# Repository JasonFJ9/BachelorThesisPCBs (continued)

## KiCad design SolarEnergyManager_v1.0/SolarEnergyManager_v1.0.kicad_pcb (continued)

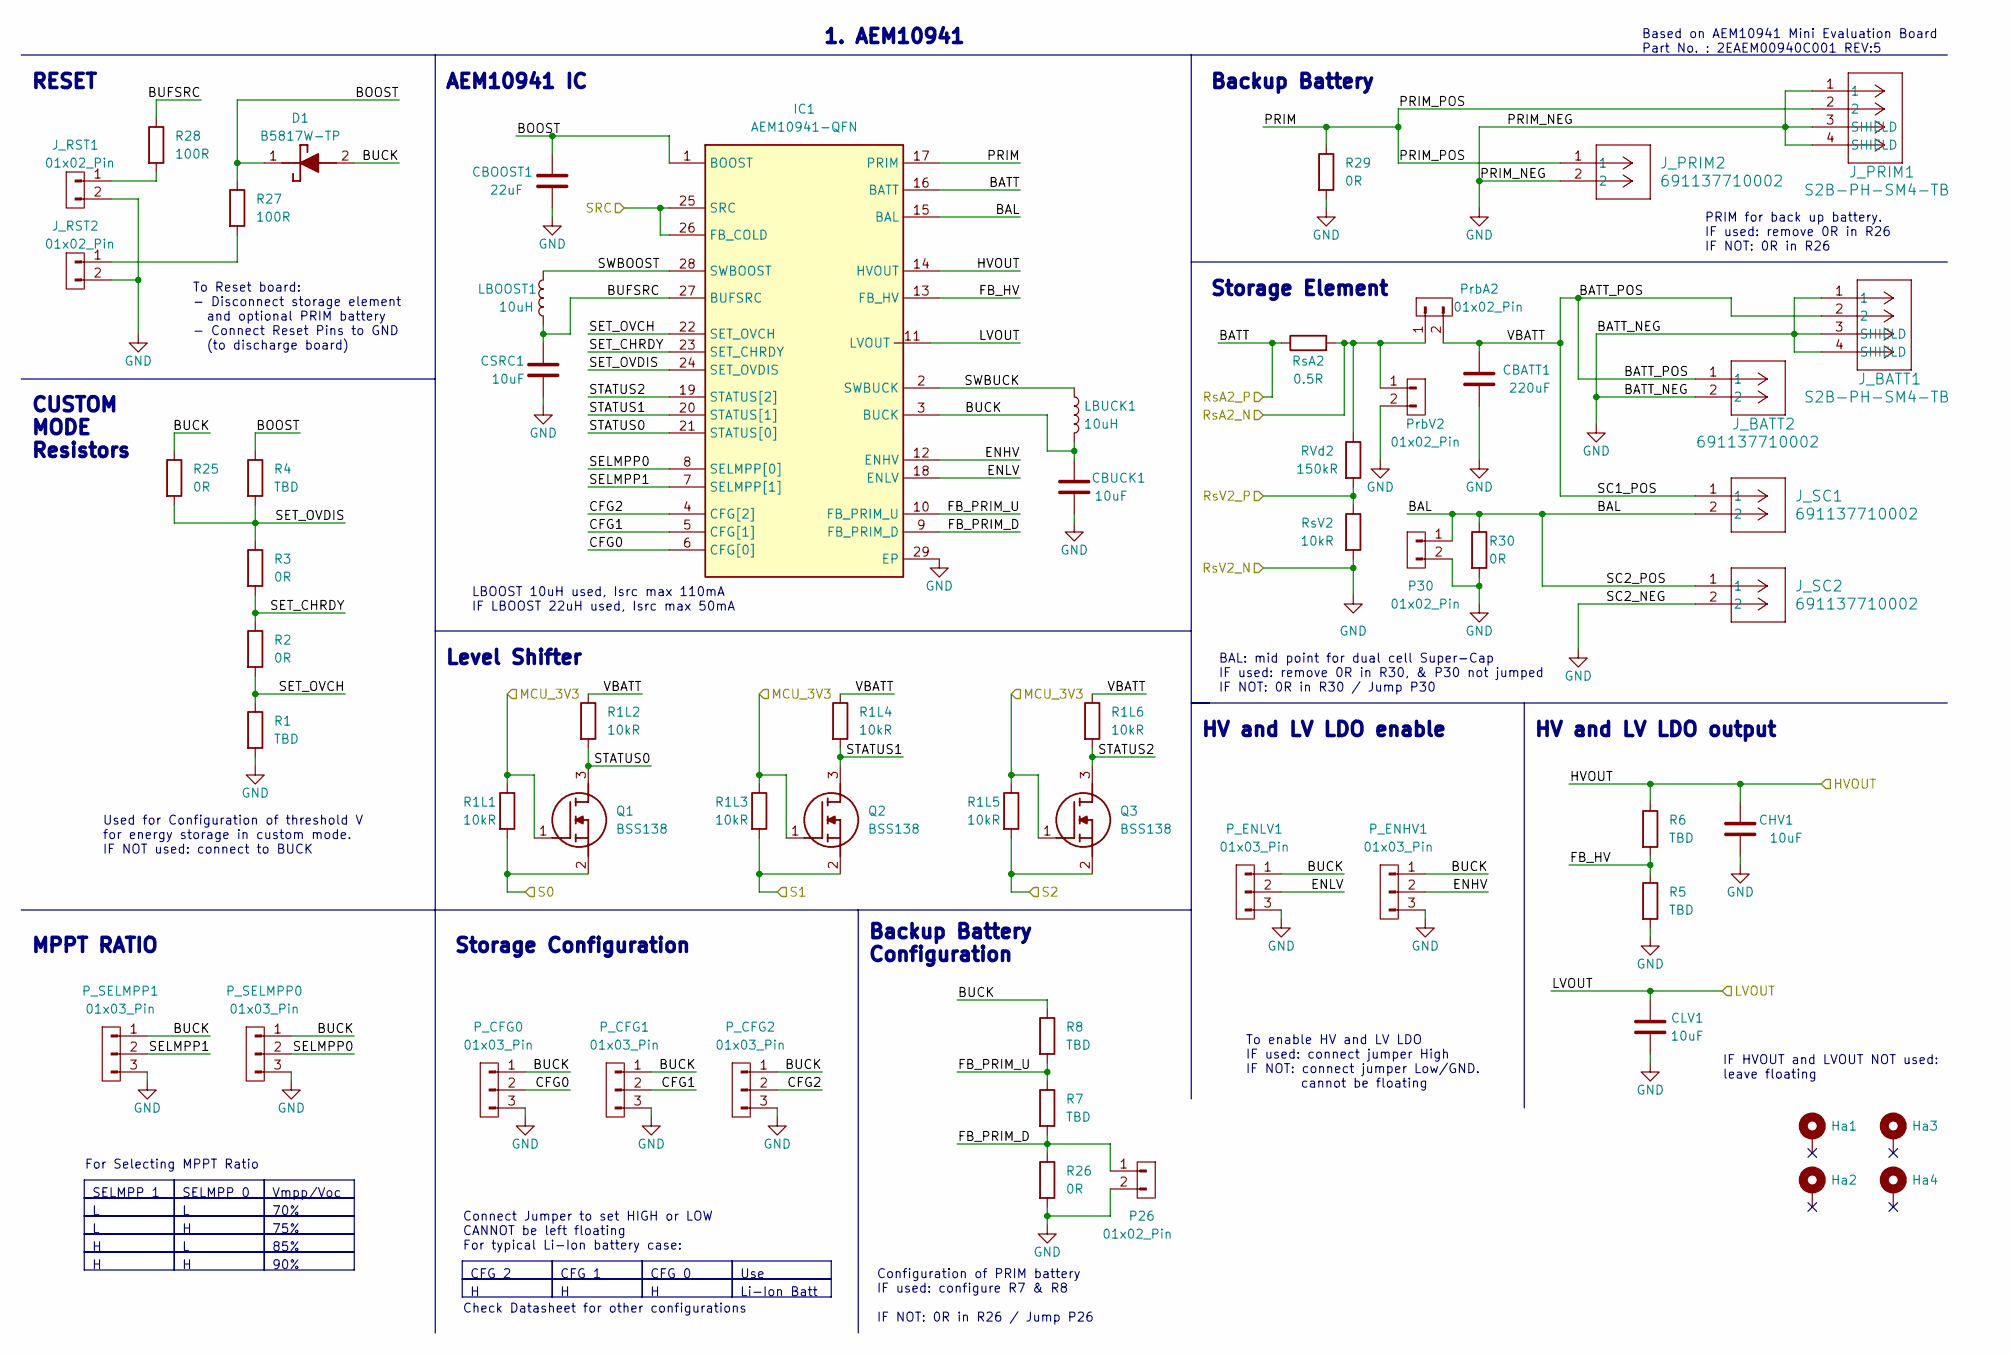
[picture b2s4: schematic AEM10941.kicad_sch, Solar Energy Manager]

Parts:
CBATT1: 220uF; C_1206_3216Metric
CBOOST1: 22uF; C_0603_1608Metric
CBUCK1: 10uF; C_0603_1608Metric
CHV1: 10uF; C_0603_1608Metric
CLV1: 10uF; C_0603_1608Metric
CSRC1: 10uF; C_0603_1608Metric
D1: B5817W-TP; SOD3716X135N; Mouser Part Number 833-B5817W-TP
Ha1, Ha2, Ha3, Ha4: MountingHole_Pad; MountingHole_3.2mm_M3_Pad
IC1: AEM10941-QFN; QFN50P500X500X90-29N-D; Mouser Part Number 120-AEM10941-QFN
J_BATT1: S2B-PH-SM4-TB; CONN_S2B-PH-SM4-TB_JST
J_BATT2: 691137710002; CONN2_710002_WRE
J_PRIM1: S2B-PH-SM4-TB; CONN_S2B-PH-SM4-TB_JST
J_PRIM2: 691137710002; CONN2_710002_WRE
J_RST1, J_RST2: 01x02_Pin; PinHeader_1x02_P2.54mm_Vertical
J_SC1, J_SC2: 691137710002; CONN2_710002_WRE
LBOOST1: 10uH; L_Vishay_IFSC-1515AH_4x4x1.8mm
LBUCK1: 10uH; L_0603_1608Metric
P26, P30: 01x02_Pin; PinHeader_1x02_P2.54mm_Vertical
P_CFG0, P_CFG1, P_CFG2: 01x03_Pin; PinHeader_1x03_P2.54mm_Vertical
P_ENHV1: 01x03_Pin; PinHeader_1x03_P2.54mm_Vertical
P_ENLV1: 01x03_Pin; PinHeader_1x03_P2.54mm_Vertical
P_SELMPP0, P_SELMPP1: 01x03_Pin; PinHeader_1x03_P2.54mm_Vertical
PrbA2: 01x02_Pin; PinHeader_1x02_P2.54mm_Vertical
PrbV2: 01x02_Pin; PinHeader_1x02_P2.54mm_Vertical
Q1, Q2, Q3: BSS138; SOT95P240X120-3N; Mouser Part Number 512-BSS138
R1, R4, R5, R6, R7, R8: TBD; R_0603_1608Metric
R1L1, R1L2, R1L3, R1L4, R1L5, R1L6: 10kR; R_0402_1005Metric
R2, R3, R25, R26, R29, R30: 0R; R_0603_1608Metric
R27, R28: 100R; R_0603_1608Metric
RVd2: 150kR; R_0402_1005Metric
RsA2: 0.5R; R_0805_2012Metric
RsV2: 10kR; R_0402_1005Metric

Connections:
/3v3_MCU: Q1.1 (G), Q2.1 (G), Q3.1 (G), R1L1.1, R1L3.1, R1L5.1; also elsewhere on the board
/AEM10941/BAL: IC1.15 (BAL), J_SC1.2, J_SC2.1, P30.1, R30.1
/AEM10941/BATT_POS: CBATT1.1, J_BATT1.2, J_BATT2.1, J_SC1.1, PrbA2.2, R1L2.1, R1L4.1, R1L6.1
/AEM10941/BOOST: CBOOST1.1, D1.1 (K), IC1.1 (BOOST), R4.1, R27.1
/AEM10941/BUCK: CBUCK1.1, D1.2 (A), IC1.3 (BUCK), LBUCK1.2, P_CFG0.1, P_CFG1.1, P_CFG2.1, P_ENHV1.1, P_ENLV1.1, P_SELMPP0.1, P_SELMPP1.1, R8.1, R25.1
/AEM10941/BUFSRC: CSRC1.1, IC1.27 (BUFSRC), LBOOST1.2, R28.1
/AEM10941/CFG0: IC1.6 (CFG[0]), P_CFG0.2
/AEM10941/CFG1: IC1.5 (CFG[1]), P_CFG1.2
/AEM10941/CFG2: IC1.4 (CFG[2]), P_CFG2.2
/AEM10941/ENHV: IC1.12 (ENHV), P_ENHV1.2
/AEM10941/ENLV: IC1.18 (ENLV), P_ENLV1.2
/AEM10941/FB_HV: IC1.13 (FB_HV), R5.1, R6.2
/AEM10941/FB_PRIM_D: IC1.9 (FB_PRIM_D), P26.1, R7.2, R26.1
/AEM10941/FB_PRIM_U: IC1.10 (FB_PRIM_U), R7.1, R8.2
/AEM10941/HVOUT: CHV1.1, IC1.14 (HVOUT), R6.1; also elsewhere on the board
/AEM10941/LVOUT: CLV1.1, IC1.11 (LVOUT); also elsewhere on the board
/AEM10941/PRIM: IC1.17 (PRIM), J_PRIM1.2, J_PRIM2.1, R29.1
/AEM10941/SELMPP0: IC1.8 (SELMPP[0]), P_SELMPP0.2
/AEM10941/SELMPP1: IC1.7 (SELMPP[1]), P_SELMPP1.2
/AEM10941/SET_CHRDY: IC1.23 (SET_CHRDY), R2.1, R3.2
/AEM10941/SET_OVCH: IC1.22 (SET_OVCH), R1.1, R2.2
/AEM10941/SET_OVDIS: IC1.24 (SET_OVDIS), R3.1, R4.2, R25.2
/AEM10941/SRC: IC1.25 (SRC), IC1.26 (FB_COLD); also elsewhere on the board
/AEM10941/STATUS0: IC1.21 (STATUS[0]), Q1.3 (D), R1L2.2
/AEM10941/STATUS1: IC1.20 (STATUS[1]), Q2.3 (D), R1L4.2
/AEM10941/STATUS2: IC1.19 (STATUS[2]), Q3.3 (D), R1L6.2
/AEM10941/SWBOOST: IC1.28 (SWBOOST), LBOOST1.1
/AEM10941/SWBUCK: IC1.2 (SWBUCK), LBUCK1.1
/AEM_S0: Q1.2 (S), R1L1.2; also elsewhere on the board
/AEM_S1: Q2.2 (S), R1L3.2; also elsewhere on the board
/AEM_S2: Q3.2 (S), R1L5.2; also elsewhere on the board
/s_3A_N: PrbA2.1, PrbV2.1, RVd2.1, RsA2.2; also elsewhere on the board
/s_3A_P: IC1.16 (BATT), RsA2.1; also elsewhere on the board
/s_4A_P: RVd2.2, RsV2.1; also elsewhere on the board
GND: CBATT1.2, CBOOST1.2, CBUCK1.2, CHV1.2, CLV1.2, CSRC1.2, IC1.29 (EP), J_BATT1.1, J_BATT1.3 (SHIELD), J_BATT1.4 (SHIELD), J_BATT2.2, J_PRIM1.1, J_PRIM1.3 (SHIELD), J_PRIM1.4 (SHIELD), J_PRIM2.2, J_RST1.2, J_RST2.2, J_SC2.2, P26.2, P30.2, P_CFG0.3, P_CFG1.3, P_CFG2.3, P_ENHV1.3, P_ENLV1.3, P_SELMPP0.3, P_SELMPP1.3, PrbV2.2, R1.2, R5.2, R26.2, R29.2, R30.2, RsV2.2; also elsewhere on the board
unnamed: J_RST1.1, R28.2
unnamed: J_RST2.1, R27.2

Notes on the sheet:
90%
Li-Ion Batt
75%
70%
Vmpp/Voc
CFG 0
CFG 2
SELMPP 0
Use
CFG 1
85%
SELMPP 1
IF HVOUT and LVOUT NOT used: leave floating
Check Datasheet for other configurations
Storage Configuration
Connect Jumper to set HIGH or LOW CANNOT be left floating For typical Li-Ion battery case:
CUSTOM MODE Resistors
For Selecting MPPT Ratio
HV and LV LDO output
RESET
HV and LV LDO enable
Backup Battery
To enable HV and LV LDO IF used: connect jumper High IF NOT: connect jumper Low/GND. cannot be floating
1. AEM10941
Based on AEM10941 Mini Evaluation Board Part No. : 2EAEM00940C001 REV:5
BAL: mid point for dual cell Super-Cap IF used: remove 0R in R30, & P30 not jumped IF NOT: 0R in R30 / Jump P30
LBOOST 10uH used, Isrc max 110mA IF LBOOST 22uH used, Isrc max 50mA
AEM10941 IC
Storage Element
To Reset board: - Disconnect storage element and optional PRIM battery - Connect Reset Pins to GND (to discharge board)
MPPT RATIO
Backup Battery Configuration
PRIM for back up battery. IF used: remove 0R in R26 IF NOT: 0R in R26
Used for Configuration of threshold V for energy storage in custom mode. IF NOT used: connect to BUCK
Level Shifter
Configuration of PRIM battery IF used: configure R7 & R8 IF NOT: 0R in R26 / Jump P26

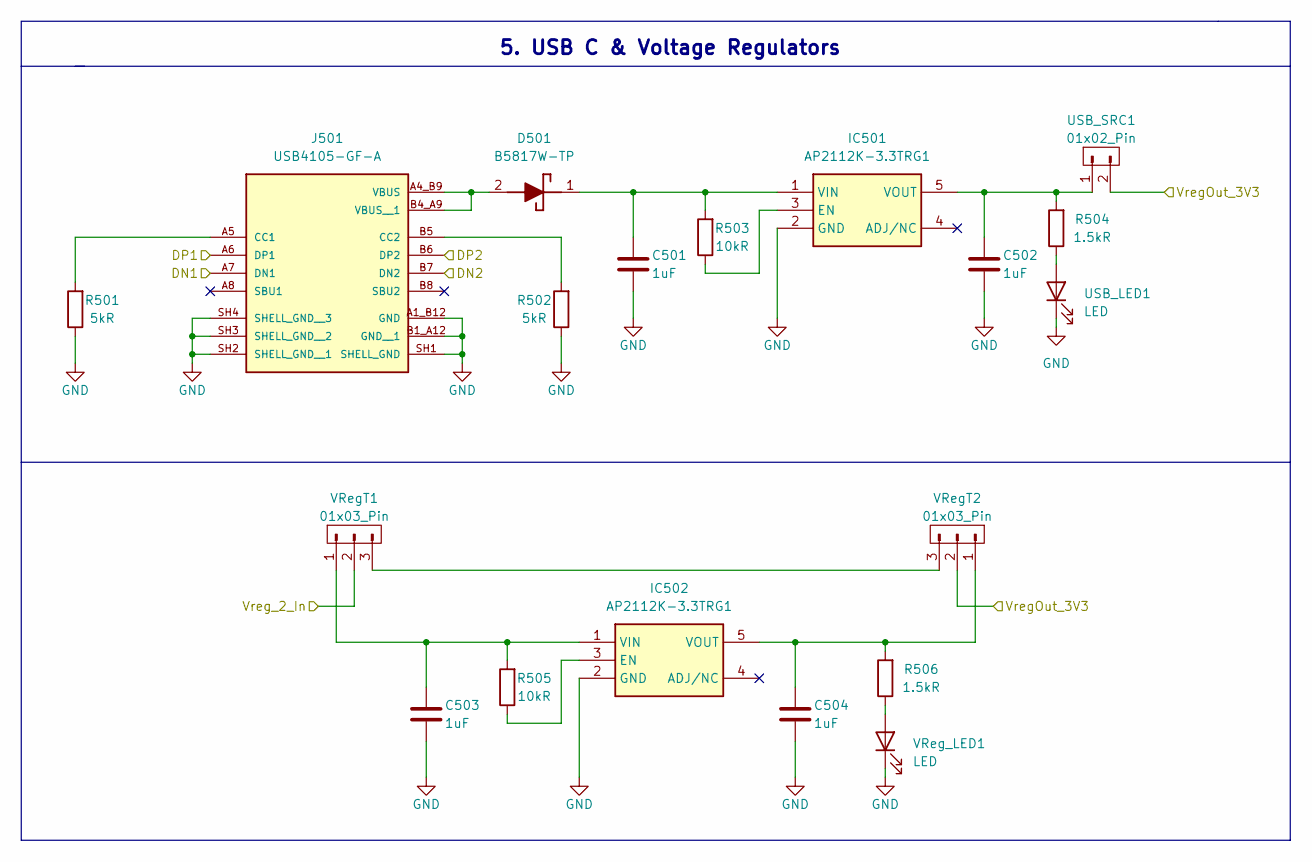
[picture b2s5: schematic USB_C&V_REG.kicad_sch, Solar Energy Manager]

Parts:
C501, C502, C503, C504: 1uF; C_0402_1005Metric
D501: B5817W-TP; SOD3716X135N; Mouser Part Number 833-B5817W-TP
IC501, IC502: AP2112K-3.3TRG1; SOT95P282X130-5N; Mouser Part Number 621-AP2112K-3.3TRG1
J501: USB4105-GF-A; GCT_USB4105-GF-A; PARTREV B3
R501, R502: 5kR; R_0402_1005Metric
R503, R505: 10kR; R_0402_1005Metric
R504, R506: 1.5kR; R_0402_1005Metric
USB_LED1: LED; LED_0402_1005Metric
USB_SRC1: 01x02_Pin; PinHeader_1x02_P2.54mm_Vertical
VRegT1, VRegT2: 01x03_Pin; PinHeader_1x03_P2.54mm_Vertical
VReg_LED1: LED; LED_0402_1005Metric

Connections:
/3v3_Vreg: USB_SRC1.2, VRegT2.2; also elsewhere on the board
/USB_D+: J501.A6 (DP1), J501.B6 (DP2); also elsewhere on the board
/USB_D-: J501.A7 (DN1), J501.B7 (DN2); also elsewhere on the board
/V_Loads: VRegT1.2; also elsewhere on the board
GND: C501.2, C502.2, C503.2, C504.2, IC501.2 (GND), IC502.2 (GND), J501.A1_B12 (GND), J501.B1_A12 (GND__1), J501.SH1 (SHELL_GND), J501.SH2 (SHELL_GND__1), J501.SH3 (SHELL_GND__2), J501.SH4 (SHELL_GND__3), R501.1, R502.1, USB_LED1.1 (K), VReg_LED1.1 (K); also elsewhere on the board
unnamed: D501.2 (A), J501.A4_B9 (VBUS), J501.B4_A9 (VBUS__1)
unnamed: C501.1, D501.1 (K), IC501.1 (VIN), R503.2
unnamed: IC501.3 (EN), R503.1
unnamed: C502.1, IC501.5 (VOUT), R504.2, USB_SRC1.1
unnamed: IC502.3 (EN), R505.1
unnamed: C503.1, IC502.1 (VIN), R505.2, VRegT1.1
unnamed: C504.1, IC502.5 (VOUT), R506.2, VRegT2.1
unnamed: J501.A5 (CC1), R501.2
unnamed: J501.B5 (CC2), R502.2
unnamed: R504.1, USB_LED1.2 (A)
unnamed: VRegT1.3, VRegT2.3
unnamed: R506.1, VReg_LED1.2 (A)

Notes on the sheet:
5. USB C & Voltage Regulators

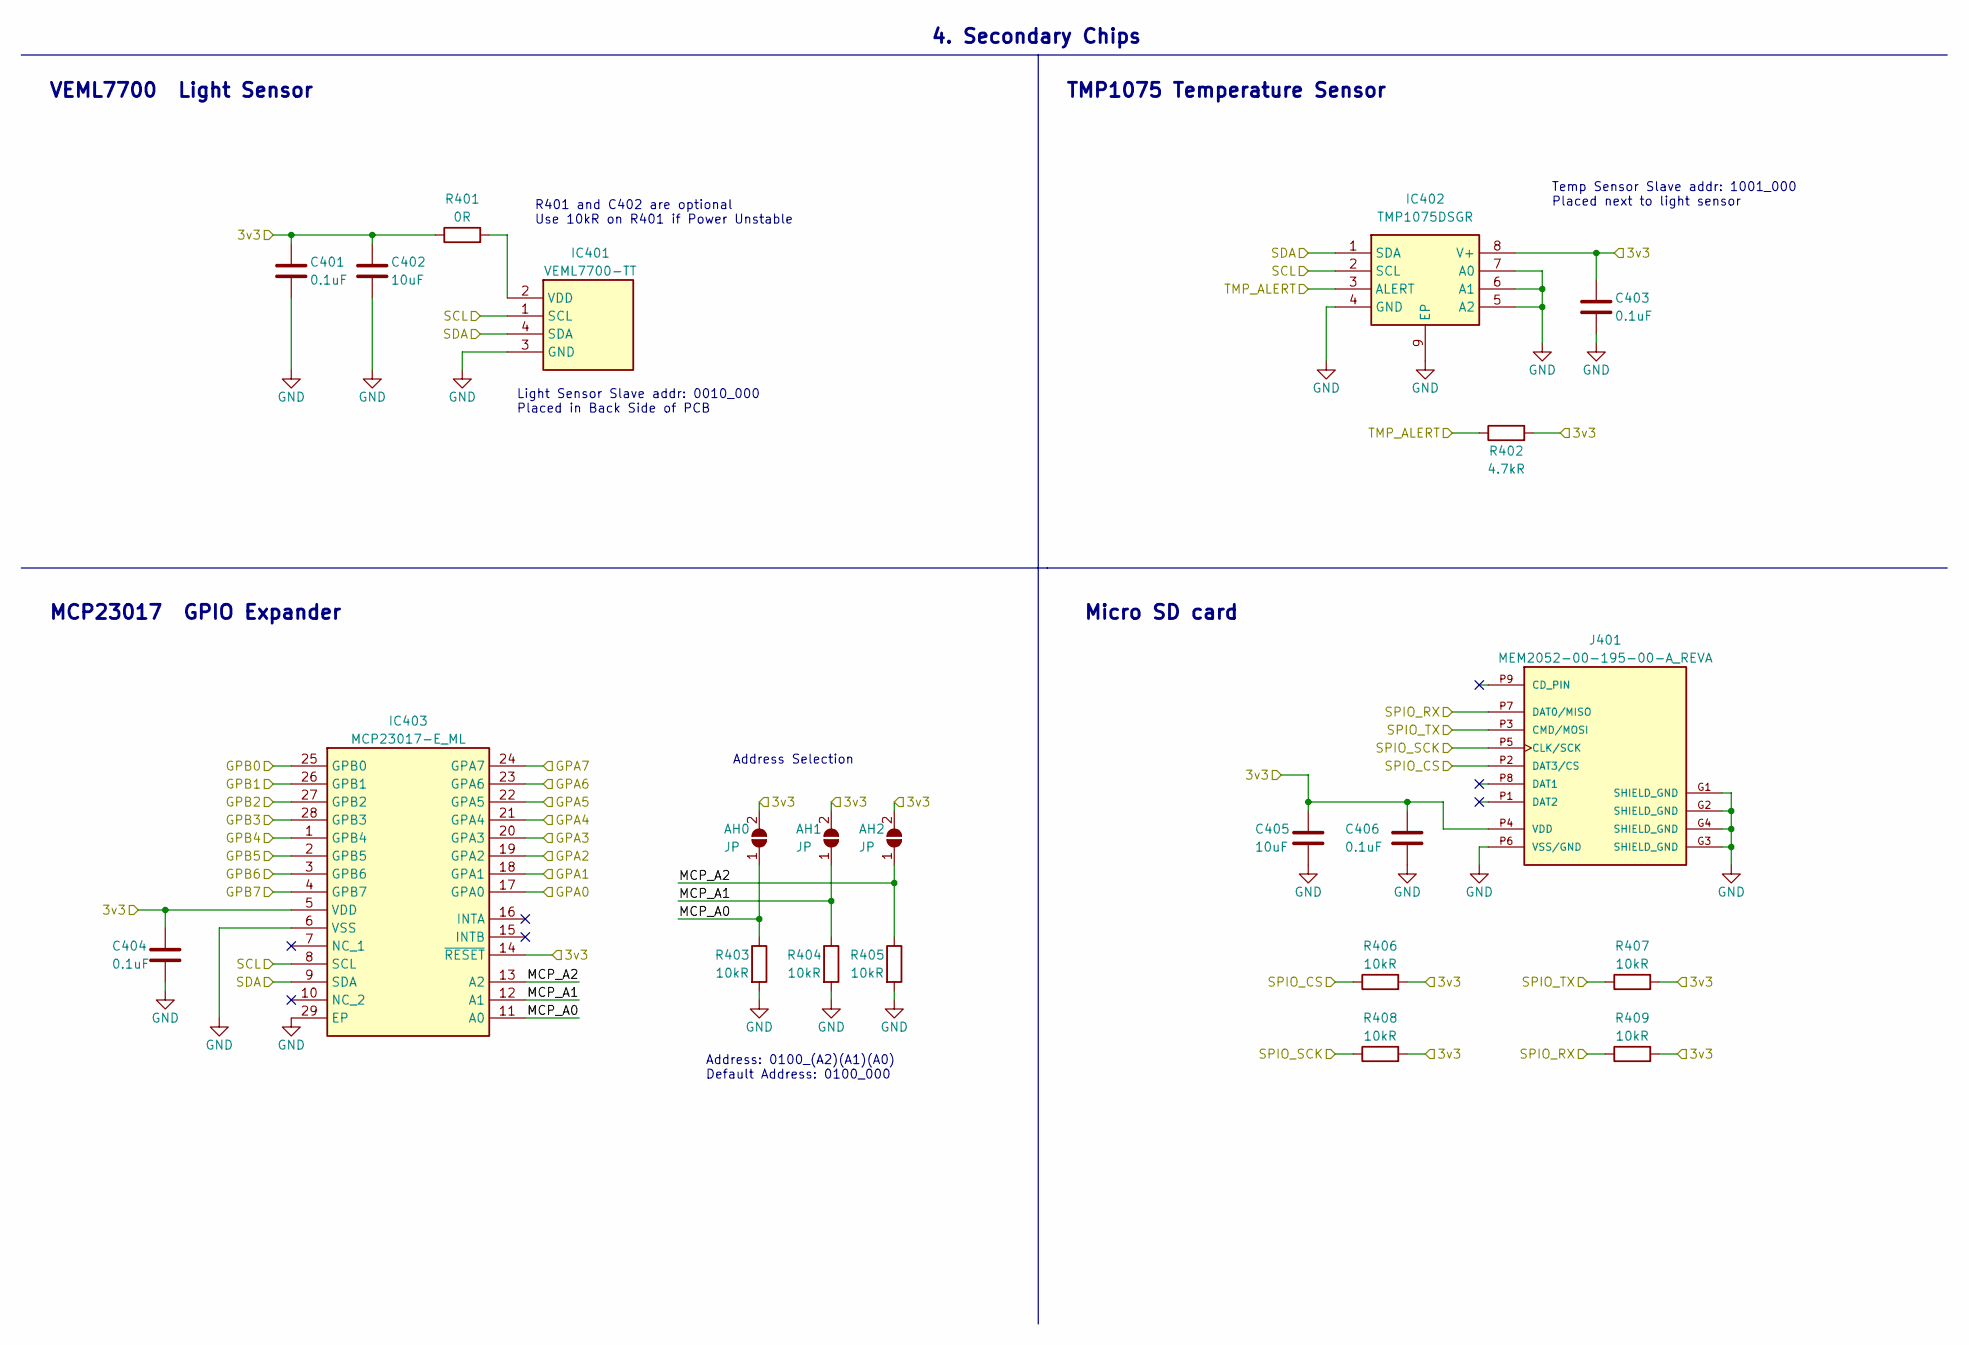
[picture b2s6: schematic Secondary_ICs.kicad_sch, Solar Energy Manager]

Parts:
AH0, AH1, AH2: JP; SolderJumper-2_P1.3mm_Open_TrianglePad1.0x1.5mm
C401, C403, C404, C406: 0.1uF; C_0402_1005Metric
C402, C405: 10uF; C_0402_1005Metric
IC401: VEML7700-TT; VEML7700; Mouser Part Number 78-VEML7700-TT
IC402: TMP1075DSGR; SON50P200X200X80-9N; Mouser Part Number 595-TMP1075DSGR
IC403: MCP23017-E_ML; QFN65P600X600X100-29N-D; Mouser Part Number 579-MCP23017-E/ML
J401: MEM2052-00-195-00-A_REVA; GCT_MEM2052-00-195-00-A_REVA; PARTREV A
R401: 0R; R_0402_1005Metric
R402: 4.7kR; R_0402_1005Metric
R403, R404, R405, R406, R407, R408, R409: 10kR; R_0402_1005Metric

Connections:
/3v3_Sec: AH0.2 (B), AH1.2 (B), AH2.2 (B), C401.1, C402.1, C403.1, C404.1, C405.1, C406.1, IC402.8 (V+), IC403.5 (VDD), IC403.14 (~RESET), J401.P4 (VDD), R401.1, R402.2, R406.2, R407.2, R408.2, R409.2; also elsewhere on the board
/GPA0: IC403.17 (GPA0); also elsewhere on the board
/GPA1: IC403.18 (GPA1); also elsewhere on the board
/GPA2: IC403.19 (GPA2); also elsewhere on the board
/GPA3: IC403.20 (GPA3); also elsewhere on the board
/GPA4: IC403.21 (GPA4); also elsewhere on the board
/GPA5: IC403.22 (GPA5); also elsewhere on the board
/GPA6: IC403.23 (GPA6)
/GPA7: IC403.24 (GPA7)
/GPB0: IC403.25 (GPB0); also elsewhere on the board
/GPB1: IC403.26 (GPB1); also elsewhere on the board
/GPB2: IC403.27 (GPB2); also elsewhere on the board
/GPB3: IC403.28 (GPB3); also elsewhere on the board
/GPB4: IC403.1 (GPB4); also elsewhere on the board
/GPB5: IC403.2 (GPB5); also elsewhere on the board
/GPIO16/SPI0_RX: J401.P7 (DAT0/MISO), R409.1; also elsewhere on the board
/GPIO17/SPI0_CS: J401.P2 (DAT3/CS), R406.1; also elsewhere on the board
/GPIO18/SPI0_SCK: J401.P5 (CLK/SCK), R408.1; also elsewhere on the board
/GPIO19/SPI0_TX: J401.P3 (CMD/MOSI), R407.1; also elsewhere on the board
/GPIO20/I2C0_SDA: IC401.4 (SDA), IC402.1 (SDA), IC403.9 (SDA); also elsewhere on the board
/GPIO21/I2C0_SCL: IC401.1 (SCL), IC402.2 (SCL), IC403.8 (SCL); also elsewhere on the board
/Gate_C_Load: IC403.4 (GPB7); also elsewhere on the board
/Gate_R_Load: IC403.3 (GPB6); also elsewhere on the board
/Secondary_ICs/MCP_A0: AH0.1 (A), IC403.11 (A0), R403.1
/Secondary_ICs/MCP_A1: AH1.1 (A), IC403.12 (A1), R404.1
/Secondary_ICs/MCP_A2: AH2.1 (A), IC403.13 (A2), R405.1
/TMP_ALERT: IC402.3 (ALERT), R402.1; also elsewhere on the board
GND: C401.2, C402.2, C403.2, C404.2, C405.2, C406.2, IC401.3 (GND), IC402.4 (GND), IC402.5 (A2), IC402.6 (A1), IC402.7 (A0), IC402.9 (EP), IC403.6 (VSS), IC403.29 (EP), J401.G1 (SHIELD_GND), J401.G2 (SHIELD_GND), J401.G3 (SHIELD_GND), J401.G4 (SHIELD_GND), J401.P6 (VSS/GND), R403.2, R404.2, R405.2; also elsewhere on the board
unnamed: IC401.2 (VDD), R401.2

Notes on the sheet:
Address Selection
TMP1075 Temperature Sensor
Temp Sensor Slave addr: 1001_000 Placed next to light sensor
R401 and C402 are optional Use 10kR on R401 if Power Unstable
Micro SD card
MCP23017 GPIO Expander
Light Sensor Slave addr: 0010_000 Placed in Back Side of PCB
Address: 0100_(A2)(A1)(A0) Default Address: 0100_000
4. Secondary Chips
VEML7700 Light Sensor

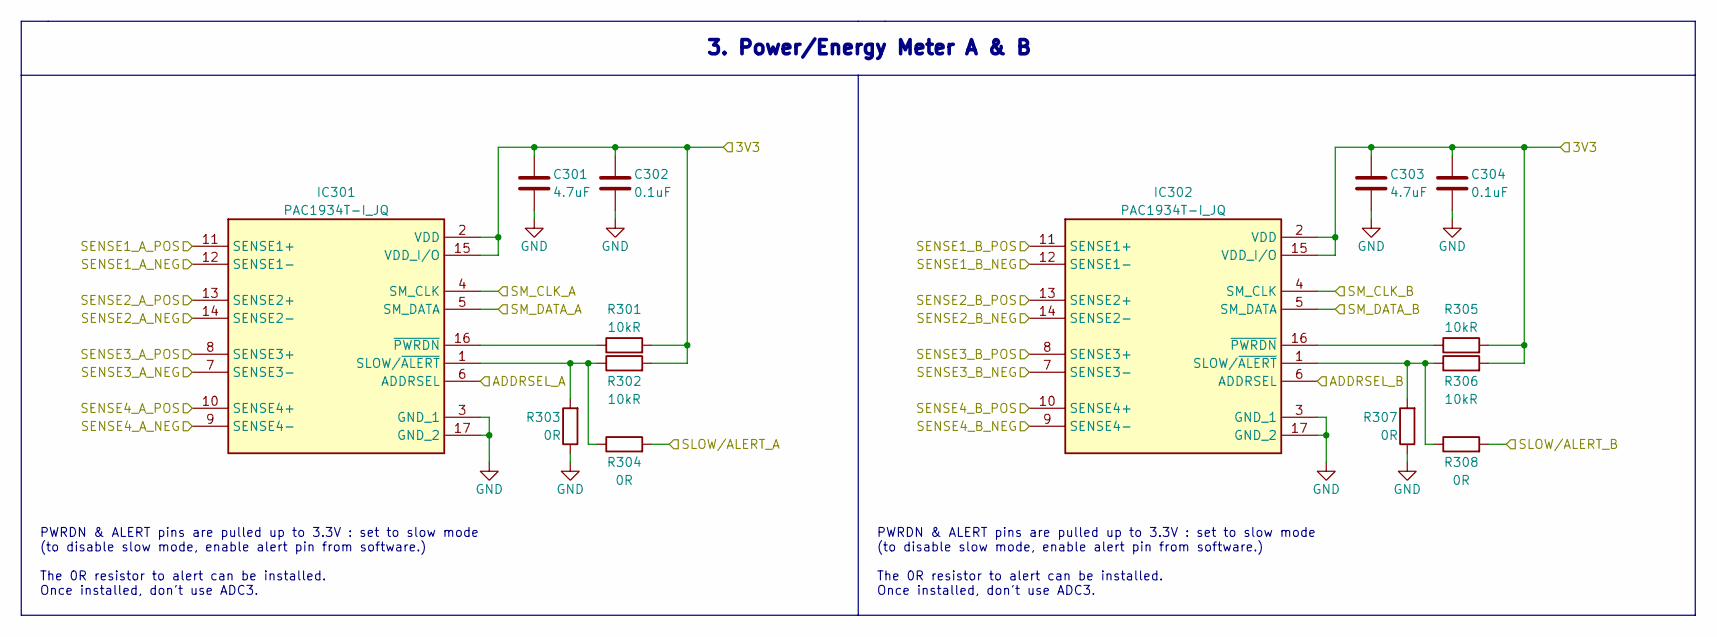
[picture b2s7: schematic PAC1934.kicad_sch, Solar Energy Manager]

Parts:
C301, C303: 4.7uF; C_0402_1005Metric
C302, C304: 0.1uF; C_0402_1005Metric
IC301, IC302: PAC1934T-I_JQ; QFN65P400X400X55-17N-D; Mouser Part Number 579-PAC1934JQ
R301, R302, R305, R306: 10kR; R_0402_1005Metric
R303, R304, R307, R308: 0R; R_0402_1005Metric

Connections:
/3v3_MCU: IC302.7 (SENSE3-); also elsewhere on the board
/3v3_Sec: C301.1, C302.1, C303.1, C304.1, IC301.2 (VDD), IC301.15 (VDD_I/O), IC302.2 (VDD), IC302.9 (SENSE4-), IC302.15 (VDD_I/O), R301.2, R302.2, R305.2, R306.2; also elsewhere on the board
/3v3_Vreg: IC302.8 (SENSE3+), IC302.10 (SENSE4+); also elsewhere on the board
/GPIO20/I2C0_SDA: IC301.5 (SM_DATA), IC302.5 (SM_DATA); also elsewhere on the board
/GPIO21/I2C0_SCL: IC301.4 (SM_CLK), IC302.4 (SM_CLK); also elsewhere on the board
/GPIO28/ADC2: R308.2; also elsewhere on the board
/GPIO29/ADC3: R304.2; also elsewhere on the board
/PAC1934/ADDRSEL_A: IC301.6 (ADDRSEL); also elsewhere on the board
/PAC1934/ADDRSEL_B: IC302.6 (ADDRSEL); also elsewhere on the board
/V_Loads: IC302.11 (SENSE1+); also elsewhere on the board
/s_1A_N: IC301.12 (SENSE1-); also elsewhere on the board
/s_1A_P: IC301.11 (SENSE1+); also elsewhere on the board
/s_1B_N: IC302.12 (SENSE1-); also elsewhere on the board
/s_2A_P: IC301.13 (SENSE2+); also elsewhere on the board
/s_2B_P: IC302.13 (SENSE2+); also elsewhere on the board
/s_3A_N: IC301.7 (SENSE3-); also elsewhere on the board
/s_3A_P: IC301.8 (SENSE3+); also elsewhere on the board
/s_4A_P: IC301.10 (SENSE4+); also elsewhere on the board
GND: C301.2, C302.2, C303.2, C304.2, IC301.3 (GND_1), IC301.9 (SENSE4-), IC301.14 (SENSE2-), IC301.17 (GND_2), IC302.3 (GND_1), IC302.14 (SENSE2-), IC302.17 (GND_2), R303.1, R307.1; also elsewhere on the board
unnamed: IC301.1 (SLOW/~ALERT), R302.1, R303.2, R304.1
unnamed: IC301.16 (~PWRDN), R301.1
unnamed: IC302.1 (SLOW/~ALERT), R306.1, R307.2, R308.1
unnamed: IC302.16 (~PWRDN), R305.1

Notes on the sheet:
PWRDN & ALERT pins are pulled up to 3.3V : set to slow mode (to disable slow mode, enable alert pin from software.) The 0R resistor to alert can be installed. Once installed, don't use ADC3.
3. Power/Energy Meter A & B

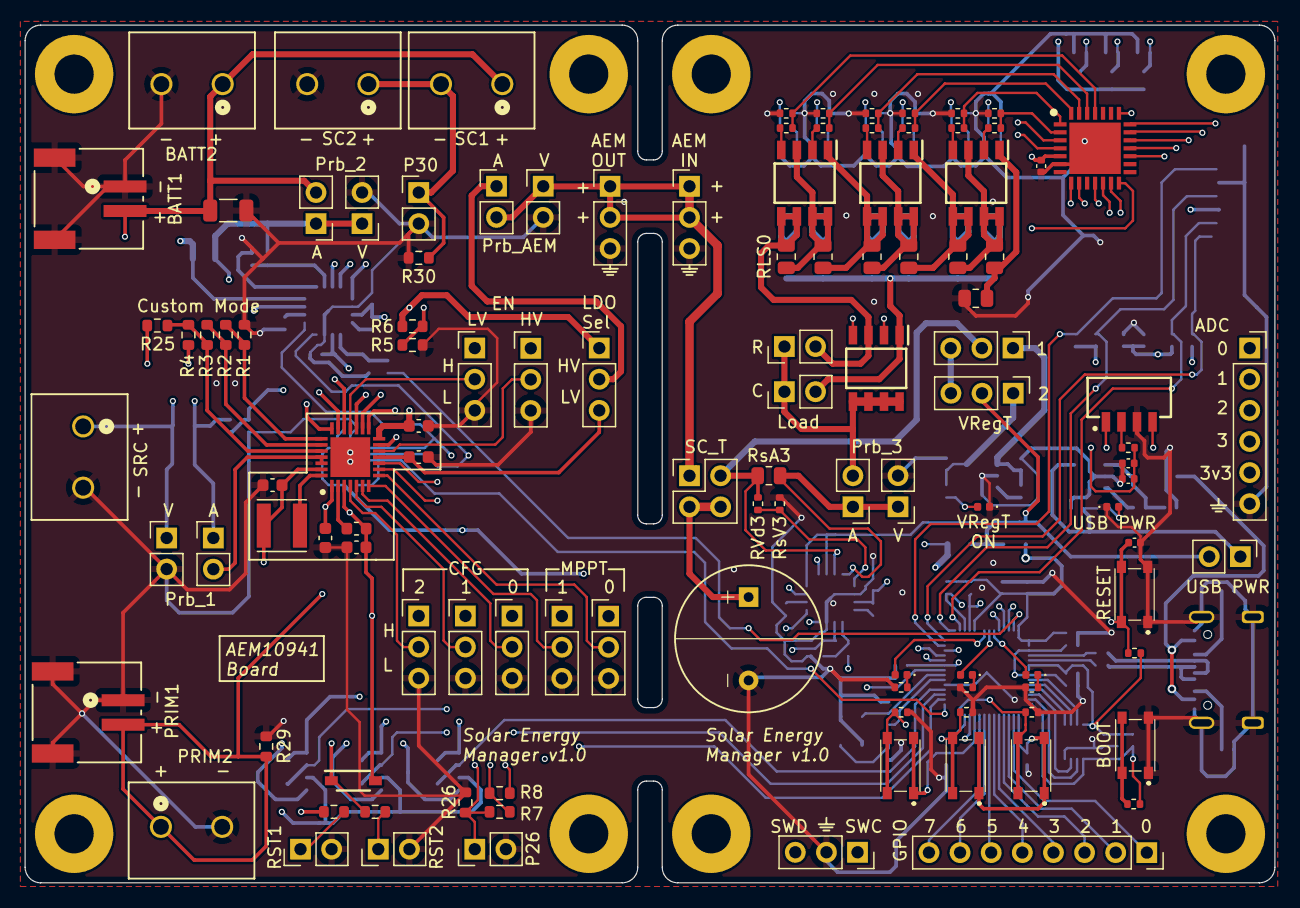
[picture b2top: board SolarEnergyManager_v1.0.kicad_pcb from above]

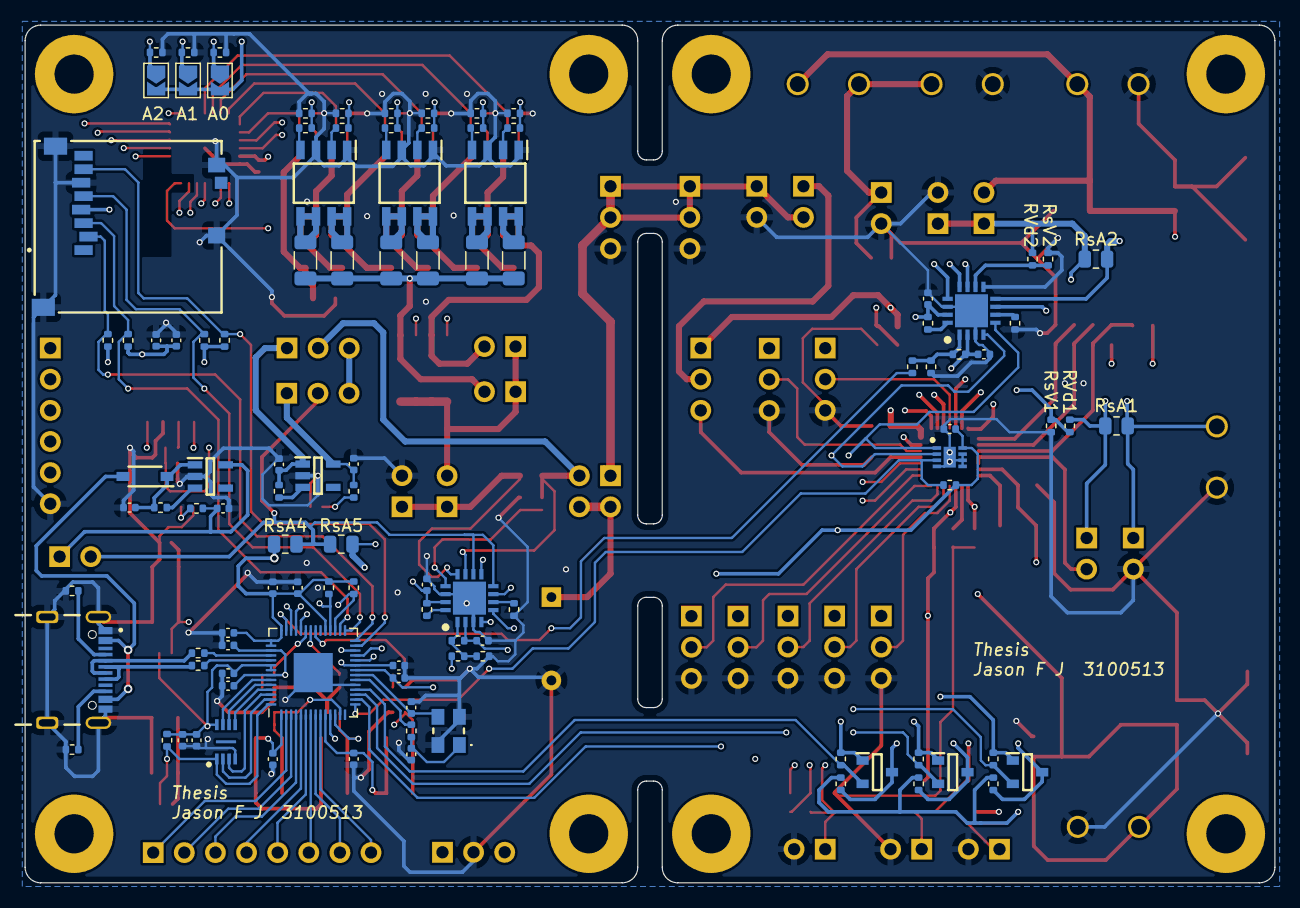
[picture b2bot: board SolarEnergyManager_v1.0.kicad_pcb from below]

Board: 4 copper layers, 102.0 x 70.0 mm, 229 parts (107 on the bottom side), 157 nets.

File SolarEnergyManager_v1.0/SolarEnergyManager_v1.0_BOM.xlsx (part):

Item | Qty | Reference(s) | Value | Footprint | Manufacturer_Part_Number | Mouser Part Number | Mouser Link
x | 0 | AH0, AH1, AH2 | JP | Jumper:SolderJumper-2_P1.3mm_Open_TrianglePad1.0x1.5mm
1 | 2 | C201, C202 | 15pF High Freq | Capacitor_SMD:C_0402_1005Metric | CBR04C150J5GACAUTO | 80-CBR04C150J5GAUTO | https://www.mouser.de/ProductDetail/KEMET/CBR04C150J5GACAUTO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
2 | 16 | C203, C204, C205, C206, C207, C208, C211, C212, C213, C215, C302, C304, C401, C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 | 0.1uF | Capacitor_SMD:C_0402_1005Metric | 0402X7R104KT7AT | 581-0402X7R104KT7AT | https://www.mouser.de/ProductDetail/KYOCERA-AVX/0402X7R104KT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
3 | 6 | C209, C210, C501, C502, C503, C504 | 1uF | Capacitor_SMD:C_0402_1005Metric | MBASL105SB5105KFNA01 | 963-BASL105SB5105KF | https://www.mouser.de/ProductDetail/TAIYO-YUDEN/MBASL105SB51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
4 | 3 | C214, C301, C303 | 4.7uF | Capacitor_SMD:C_0402_1005Metric | GRT155C81A475ME13D | 81-GRT155C81A475ME3D | https://www.mouser.de/ProductDetail/Murata-Electronics/GRT15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
5 | 2 | C402, C405 | 10uF | Capacitor_SMD:C_0402_1005Metric | GRT155R60J106ME13J | 81-GRT155R60J106ME13 | https://www.mouser.de/ProductDetail/Murata-Electronics/GRT15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
x | 0 | C_Load1, J_RST1, J_RST2, P26, P30, PrbA1, PrbA2, PrbA3, PrbA_AEM1, PrbV1, PrbV2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 | 01x02_Pin | Connector_PinHeader_2.54mm:PinHeader_1x02_P2.54mm_Vertical
6 | 2 | CBATT1, CLP5 | 220uF | Capacitor_SMD:C_1206_3216Metric | GRM31CR60J227ME11K | 81-GRM31CR60J227ME1K | https://www.mouser.de/ProductDetail/Murata-Electronics/GRM31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
7 | 1 | CBOOST1 | 22uF | Capacitor_SMD:C_0603_1608Metric | MSASJ168BB5226MTNA01 | 963-MSASJ168BB5226MT | https://www.mouser.de/ProductDetail/TAIYO-YUDEN/MSASJ168BB52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
8 | 4 | CBUCK1, CHV1, CLV1, CSRC1 | 10uF | Capacitor_SMD:C_0603_1608Metric | MSASJ168AB5106KTNA01 | 963-MSASJ168AB5106KT | https://www.mouser.de/ProductDetail/TAIYO-YUDEN/MSASJ168AB51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
9 | 1 | CLP0 | 1uF | Capacitor_SMD:C_1206_3216Metric | 12066C105KAT2A | 581-12066C105KAT2A | https://www.mouser.de/ProductDetail/KYOCERA-AVX/12066C105KAT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
10 | 1 | CLP1 | 10uF | Capacitor_SMD:C_1206_3216Metric | 12066G106ZAT4A | 581-12066G106ZAT4A | https://www.mouser.de/ProductDetail/KYOCERA-AVX/12066G106ZAT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
11 | 1 | CLP2 | 47uF | Capacitor_SMD:C_1206_3216Metric | JMK316ABJ476ML8T | 963-JMK316ABJ476ML8T | https://www.mouser.de/ProductDetail/TAIYO-YUDEN/JMK316ABJ476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
12 | 2 | CLP3, CLP4 | 100uF | Capacitor_SMD:C_1206_3216Metric | MSASJ31LAB5107MTNA01 | 963-MSASJ31LAB5107MT | https://www.mouser.de/ProductDetail/TAIYO-YUDEN/MSASJ31LAB51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
x | 0 | CLP4 | 150uF | Capacitor_SMD:C_1206_3216Metric | none | none
13 | 2 | D1, D501 | B5817W-TP | B5817W-TP:SOD3716X135N | B5817W-TP | 833-B5817W-TP | https://www.mouser.de/ProductDetail/Micro-Commercial-Compone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
14 | 5 | D201, D202, D203, USB_LED1, VReg_LED1 | LED | LED_SMD:LED_0402_1005Metric | LB QH9G-N1OO-35-1 | 720-LBQH9G-N1P2-35-1 | https://www.mouser.de/ProductDetail/ams-OSRAM/LB-QH9G-N1OO-3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
x | 0 | H1, H2, H3, H4, Ha1, Ha2, Ha3, Ha4 | MountingHole_Pad | MountingHole:MountingHole_3.2mm_M3_Pad
15 | 1 | IC1 | AEM10941-QFN | AEM10941-QFN:QFN50P500X500X90-29N-D | AEM10941-QFN | 120-AEM10941-QFN | https://www.mouser.de/ProductDetail/e-peas/AEM10941-QFN?qs=W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
16 | 1 | IC201 | RP2040 | Package_DFN_QFN:QFN-56-1EP_7x7mm_P0.4mm_EP3.2x3.2mm | SC0914(13) | 358-SC091413 | https://www.mouser.de/ProductDetail/Raspberry-Pi/SC091413?qs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
17 | 1 | IC202 | W25Q16JVUXIQ_TR | W25Q16JVUXIQ_TR:SON50P300X200X60-9N | W25Q16JVUXIQ TR | 454-W25Q16JVUXIQTR | https://www.mouser.de/ProductDetail/Winbond/W25Q16JVUXIQ-TR?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
18 | 2 | IC301, IC302 | PAC1934T-I_JQ | PAC1934T-I_JQ:QFN65P400X400X55-17N-D | PAC1934T-I/JQ | 579-PAC1934JQ | https://www.mouser.de/ProductDetail/Microchip-Technology/PAC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
19 | 1 | IC401 | VEML7700-TT | VEML7700-TT:VEML7700 | VEML7700-TT | 78-VEML7700-TT | https://www.mouser.de/ProductDetail/Vishay-Semiconductors/VE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
20 | 1 | IC402 | TMP1075DSGR | TMP1075DSGR:SON50P200X200X80-9N | TMP1075DSGR | 595-TMP1075DSGR | https://www.mouser.de/ProductDetail/Texas-Instruments/TMP107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
21 | 1 | IC403 | MCP23017-E_ML | MCP23017-E_ML:QFN65P600X600X100-29N-D | MCP23017-E/ML | 579-MCP23017-E/ML | https://www.mouser.de/ProductDetail/Microchip-Technology/MCP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
22 | 2 | IC501, IC502 | AP2112K-3.3TRG1 | AP2112K-3.3TRG1:SOT95P282X130-5N | AP2112K-3.3TRG1 | 621-AP2112K-3.3TRG1 | https://www.mouser.de/ProductDetail/Diodes-Incorporated/AP21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
x | 0 | J201 | Conn_01x03_Pin | Connector_PinSocket_2.54mm:PinSocket_1x03_P2.54mm_Vertical
x | 0 | J202 | Conn_01x06_Pin | Connector_PinSocket_2.54mm:PinSocket_1x06_P2.54mm_Vertical
x | 0 | J203 | Conn_01x08_Pin | Connector_PinSocket_2.54mm:PinSocket_1x08_P2.54mm_Vertical
23 | 1 | J401 | MEM2052-00-195-00-A_REVA | MEM2052-00-195-00-A_REVA:GCT_MEM2052-00-195-00-A_REVA | MEM2052-00-195-00-A | 640-MEM20520019500A | https://www.mouser.de/ProductDetail/GCT/MEM2052-00-195-00-A?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
24 | 1 | J501 | USB4105-GF-A | USB4105_GF_A:GCT_USB4105-GF-A | USB4105-GF-A | 640-USB4105-GF-A | https://www.mouser.de/ProductDetail/GCT/USB4105-GF-A?qs=KUoI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
x | 0 | J_AEM_OUT1, J_AEM_OUT2, LDO1, P_CFG0, P_CFG1, P_CFG2, P_ENHV1, P_ENLV1, P_SELMP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 | 01x03_Pin | Connector_PinHeader_2.54mm:PinHeader_1x03_P2.54mm_Vertical
x | 2 | J_BATT1, J_PRIM1 | S2B-PH-SM4-TB | S2B_PH_SM4_TB:CONN_S2B-PH-SM4-TB_JST
25 | 5 | J_BATT2, J_PRIM2, J_SC1, J_SC2, J_SRC1 | 691137710002 | 691137710002:CONN2_710002_WRE | 691137710002 | 710-691137710002 | https://www.mouser.de/ProductDetail/Wurth-Elektronik/6911377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
26 | 1 | LBOOST1 | 10uH | Inductor_SMD:L_Vishay_IFSC-1515AH_4x4x1.8mm | LPS4018-103MRC | 994-LPS4018-103MRC | https://www.mouser.de/ProductDetail/Coilcraft/LPS4018-103MRC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
27 | 1 | LBUCK1 | 10uH | Inductor_SMD:L_0603_1608Metric | MLZ1608M100WTD25 | 810-MLZ1608M100WTD25 | https://www.mouser.de/ProductDetail/TDK/MLZ1608M100WTD25?qs=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
28 | 3 | Q1, Q2, Q3 | BSS138 | BSS138:SOT95P240X120-3N | BSS138 | 512-BSS138 | https://www.mouser.de/ProductDetail/onsemi-Fairchild/BSS138?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
29 | 7 | Q6S12, Q601, Q602, Q603, Q604, Q605, Q606 | SI4204DY-T1-GE3 | SI4204DY-T1-GE3:SOIC127P600X175-8N | SI4204DY-T1-GE3 | 781-SI4204DY-T1-GE3 | https://www.mouser.de/ProductDetail/Vishay-Semiconductors/SI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
x | 0 | R1, R4, R5, R6, R7, R8 | TBD | Resistor_SMD:R_0603_1608Metric
30 | 38 | R1L1, R1L2, R1L3, R1L4, R1L5, R1L6 R209, R210, R211, R212, R301, R302, R305, R3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 | 10kR (35) nT; (3) 1% | Resistor_SMD:R_0402_1005Metric | RCC040210K0FKED | 71-RCC040210K0FKED | https://www.mouser.de/ProductDetail/Vishay-Dale/RCC040210K0F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
31 | 6 | R2, R3, R25, R26, R29, R30 | 0R | Resistor_SMD:R_0603_1608Metric | RCC06030000Z0EA | 71-RCC06030000Z0EA | https://www.mouser.de/ProductDetail/Vishay-Dale/RCC06030000Z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
32 | 2 | R27, R28 | 100R | Resistor_SMD:R_0603_1608Metric | SDR03EZPF1000 | 755-SDR03EZPF1000 | https://www.mouser.de/ProductDetail/ROHM-Semiconductor/SDR03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
33 | 2 | R201, R202 | 27R 1% HiP | Resistor_SMD:R_0402_1005Metric | CR0402-FX-27R0GLF | 652-CR0402FX-27R0GLF | https://www.mouser.de/ProductDetail/Bourns/CR0402-FX-27R0GLF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
34 | 13 | R203, R601, R602, R603, R604, R605, R606, R613, R614, R615, R616, R617, R618 | 1kR | Resistor_SMD:R_0402_1005Metric | CRCW04021K00FKED | 71-CRCW0402-1.0K-E3 | https://www.mouser.de/ProductDetail/Vishay-Dale/CRCW04021K00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
35 | 5 | R204, R205, R206, R504, R506 | 1.5kR | Resistor_SMD:R_0402_1005Metric | CR0402-FX-1501GLF | 652-CR0402FX-1501GLF | https://www.mouser.de/ProductDetail/Bourns/CR0402-FX-1501GLF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
36 | 2 | R207, RA1 | 499R 1% | Resistor_SMD:R_0402_1005Metric | CR0402-FX-4990GLF | 652-CR0402FX-4990GLF | https://www.mouser.de/ProductDetail/Bourns/CR0402-FX-4990GLF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
37 | 1 | R208 | 2kR | Resistor_SMD:R_0402_1005Metric | 560112110064 | 710-560112110064 | https://www.mouser.de/ProductDetail/Wurth-Elektronik/5601121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
38 | 3 | R213, R214, R402 | 4.7kR | Resistor_SMD:R_0402_1005Metric | 560112110245 | 710-560112110245 | https://www.mouser.de/ProductDetail/Wurth-Elektronik/5601121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
39 | 5 | R303, R304, R307, R308, R401 | 0R | Resistor_SMD:R_0402_1005Metric | RCA04020000ZSED | 71-RCA04020000ZSED | https://www.mouser.de/ProductDetail/Vishay-Draloric/RCA04020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
